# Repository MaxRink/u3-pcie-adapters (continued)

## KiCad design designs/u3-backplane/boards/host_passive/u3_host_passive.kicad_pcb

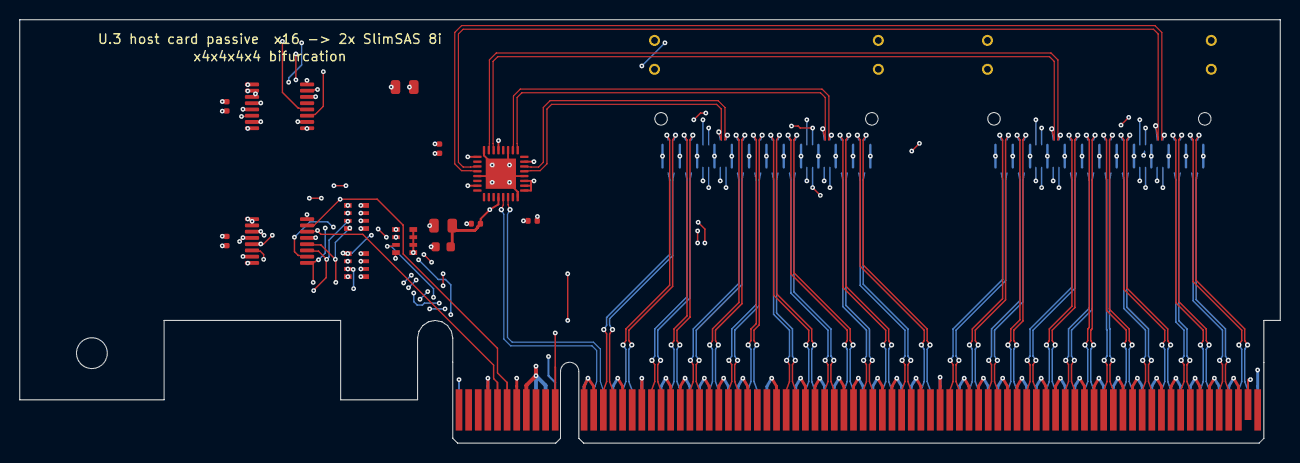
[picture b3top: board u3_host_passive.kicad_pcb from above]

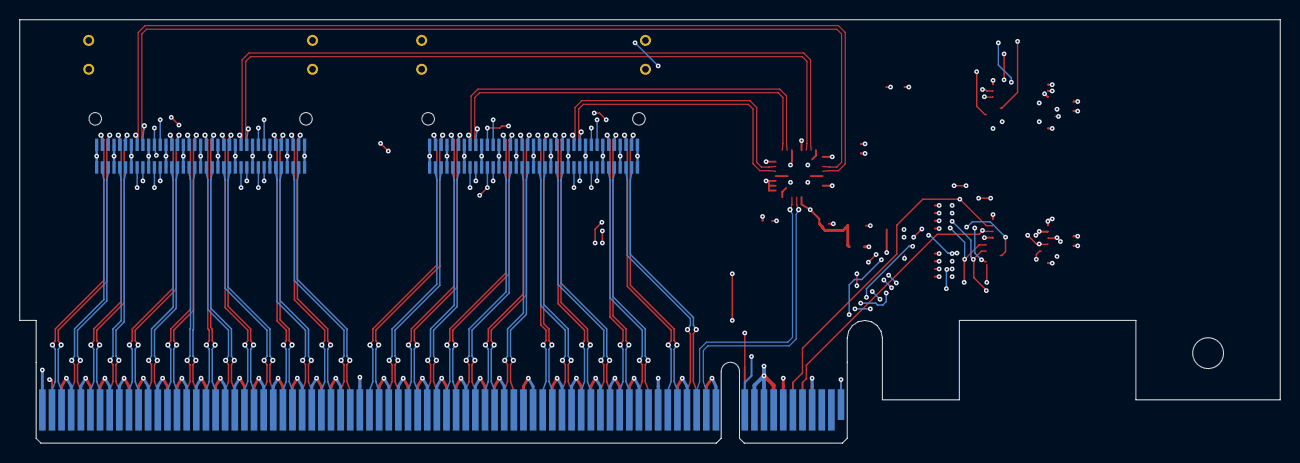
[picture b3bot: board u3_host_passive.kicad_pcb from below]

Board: 6 copper layers, 131.0 x 44.0 mm, 18 parts (2 on the bottom side), 102 nets.

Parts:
C1, C2, C4, C5, C6: 100nF; C_0402_1005Metric
C3, C7: 10uF 25V X5R; C_0805_2012Metric
FB1: ferrite 600R@100MHz; L_0603_1608Metric
H1: bracket; MountingHole_3.2mm_M3
J1: PCIe x16 edge; BUS_PCIexpress_x16
J2, J3: U10A474240T; Amphenol_U10A474_SlimSAS_8i_SFF-8654_RA_SMD
RN1, RN2: 4.7k x4; R_Array_Convex_4x0603
RN3: 33R x4; R_Array_Convex_4x0603
U1: 9DBL0442BKILF; VQFN-32-1EP_5x5mm_P0.5mm_EP3.15x3.15mm
U2: TCA9546APWR; TSSOP-16_4.4x5mm_P0.65mm
U3: TCA9554PWR; TSSOP-16_4.4x5mm_P0.65mm

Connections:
3V3: C1.2, C2.2, C3.1, C4.1, C5.1, FB1.1, J1.A9, J1.A10, J1.B8, RN1.5, RN1.6, RN1.7, RN1.8, RN2.5, RN2.6, RN2.7, RN2.8, U1.9, U1.10, U1.11, U1.15, U1.25, U1.31, U2.1, U2.2, U2.13, U2.16, U3.1, U3.2, U3.3, U3.16
3V3_A: C6.2, C7.2, FB1.2, U1.4, U1.21
GND: C1.1, C2.1, C3.2, C4.2, C5.2, C6.1, C7.1, J1.A4, J1.A12, J1.A15, J1.A18, J1.A20, J1.A23, J1.A24, J1.A27, J1.A28, J1.A31, J1.A34, J1.A37, J1.A38, J1.A41, J1.A42, J1.A45, J1.A46, J1.A49, J1.A51, J1.A54, J1.A55, J1.A58, J1.A59, J1.A62, J1.A63, J1.A66, J1.A67, J1.A70, J1.A71, J1.A74, J1.A75, J1.A78, J1.A79, J1.A82, J1.B4, J1.B7, J1.B12, J1.B13, J1.B16, J1.B18, J1.B21, J1.B22, J1.B25, J1.B26, J1.B29, J1.B32, J1.B35, J1.B36, J1.B39, J1.B40, J1.B43, J1.B44, J1.B47, J1.B49, J1.B52, J1.B53, J1.B56, J1.B57, J1.B60, J1.B61, J1.B64, J1.B65, J1.B68, J1.B69, J1.B72, J1.B73, J1.B76, J1.B77, J1.B80, J2.A1, J2.A4, J2.A7, J2.A10, J2.A13, J2.A16, J2.A19, J2.A22, J2.A25, J2.A28, J2.A31, J2.A34, J2.A37, J2.B1, J2.B4, J2.B7, J2.B10, J2.B13, J2.B16, J2.B19, J2.B22, J2.B25, J2.B28, J2.B31, J2.B34, J2.B37, J2.SH, J3.A1, J3.A4, J3.A7, J3.A10, J3.A13, J3.A16, J3.A19, J3.A22, J3.A25, J3.A28, J3.A31, J3.A34, J3.A37, J3.B1, J3.B4, J3.B7, J3.B10, J3.B13, J3.B16, J3.B19, J3.B22, J3.B25, J3.B28, J3.B31, J3.B34, J3.B37, J3.SH, U1.8, U1.12, U1.19, U1.24, U1.29, U1.33, U2.8, U3.8
P0_BPTYPE: J2.A8, U3.9
P0_CPRSNT_N: J2.B12, U3.4
P0_PERST_N: J2.B11, RN3.1
P0_SCL: J2.B8, RN1.2, U2.5
P0_SDA: J2.B9, RN1.1, U2.4
P1_BPTYPE: J2.A26, U3.10
P1_CPRSNT_N: J2.B30, U3.5
P1_PERST_N: J2.B29, RN3.2
P1_SCL: J2.B26, RN1.4, U2.7
P1_SDA: J2.B27, RN1.3, U2.6
P2_BPTYPE: J3.A8, U3.11
P2_CPRSNT_N: J3.B12, U3.6
P2_PERST_N: J3.B11, RN3.3
P2_SCL: J3.B8, RN2.2, U2.10
P2_SDA: J3.B9, RN2.1, U2.9
P3_BPTYPE: J3.A26, U3.12
P3_CPRSNT_N: J3.B30, U3.7
P3_PERST_N: J3.B29, RN3.4
P3_SCL: J3.B26, RN2.4, U2.12
P3_SDA: J3.B27, RN2.3, U2.11
PCIE_RST_N: J1.A11, RN3.5, RN3.6, RN3.7, RN3.8, U2.3
PCIE_WAKE_N: J1.B11, J2.A9, J2.A27, J3.A9, J3.A27
PER0_N: J1.A17, J2.A3
PER0_P: J1.A16, J2.A2
PER1_N: J1.A22, J2.A6
PER1_P: J1.A21, J2.A5
PER2_N: J1.A26, J2.A15
PER2_P: J1.A25, J2.A14
PER3_N: J1.A30, J2.A18
PER3_P: J1.A29, J2.A17
PER4_N: J1.A36, J2.A21
PER4_P: J1.A35, J2.A20
PER5_N: J1.A40, J2.A24
PER5_P: J1.A39, J2.A23
PER6_N: J1.A44, J2.A33
PER6_P: J1.A43, J2.A32
PER7_N: J1.A48, J2.A36
PER7_P: J1.A47, J2.A35
PER8_N: J1.A53, J3.A3
PER8_P: J1.A52, J3.A2
PER9_N: J1.A57, J3.A6
PER9_P: J1.A56, J3.A5
PER10_N: J1.A61, J3.A15
PER10_P: J1.A60, J3.A14
PER11_N: J1.A65, J3.A18
PER11_P: J1.A64, J3.A17
PER12_N: J1.A69, J3.A21
PER12_P: J1.A68, J3.A20
PER13_N: J1.A73, J3.A24
PER13_P: J1.A72, J3.A23
PER14_N: J1.A77, J3.A33
PER14_P: J1.A76, J3.A32
PER15_N: J1.A81, J3.A36
PER15_P: J1.A80, J3.A35
PET0_N: J1.B15, J2.B3
PET0_P: J1.B14, J2.B2
PET1_N: J1.B20, J2.B6
PET1_P: J1.B19, J2.B5
PET2_N: J1.B24, J2.B15
PET2_P: J1.B23, J2.B14
PET3_N: J1.B28, J2.B18
PET3_P: J1.B27, J2.B17
PET4_N: J1.B34, J2.B21
PET4_P: J1.B33, J2.B20
PET5_N: J1.B38, J2.B24
PET5_P: J1.B37, J2.B23
PET6_N: J1.B42, J2.B33
PET6_P: J1.B41, J2.B32
PET7_N: J1.B46, J2.B36
PET7_P: J1.B45, J2.B35
PET8_N: J1.B51, J3.B3
PET8_P: J1.B50, J3.B2
PET9_N: J1.B55, J3.B6
PET9_P: J1.B54, J3.B5
PET10_N: J1.B59, J3.B15
PET10_P: J1.B58, J3.B14
PET11_N: J1.B63, J3.B18
PET11_P: J1.B62, J3.B17
PET12_N: J1.B67, J3.B21
PET12_P: J1.B66, J3.B20
PET13_N: J1.B71, J3.B24
PET13_P: J1.B70, J3.B23
PET14_N: J1.B75, J3.B33
PET14_P: J1.B74, J3.B32
PET15_N: J1.B79, J3.B36
PET15_P: J1.B78, J3.B35
PRSNT_N: J1.A1, J1.B81
REFCLK0_N: J2.A12, U1.14
REFCLK0_P: J2.A11, U1.13
REFCLK1_N: J2.A30, U1.18
REFCLK1_P: J2.A29, U1.17
REFCLK2_N: J3.A12, U1.23
REFCLK2_P: J3.A11, U1.22
REFCLK3_N: J3.A30, U1.28
REFCLK3_P: J3.A29, U1.27
REFCLK_IN_N: J1.A14, U1.6
REFCLK_IN_P: J1.A13, U1.5
SMCLK: J1.B5, U2.14, U3.14
SMDAT: J1.B6, U2.15, U3.15

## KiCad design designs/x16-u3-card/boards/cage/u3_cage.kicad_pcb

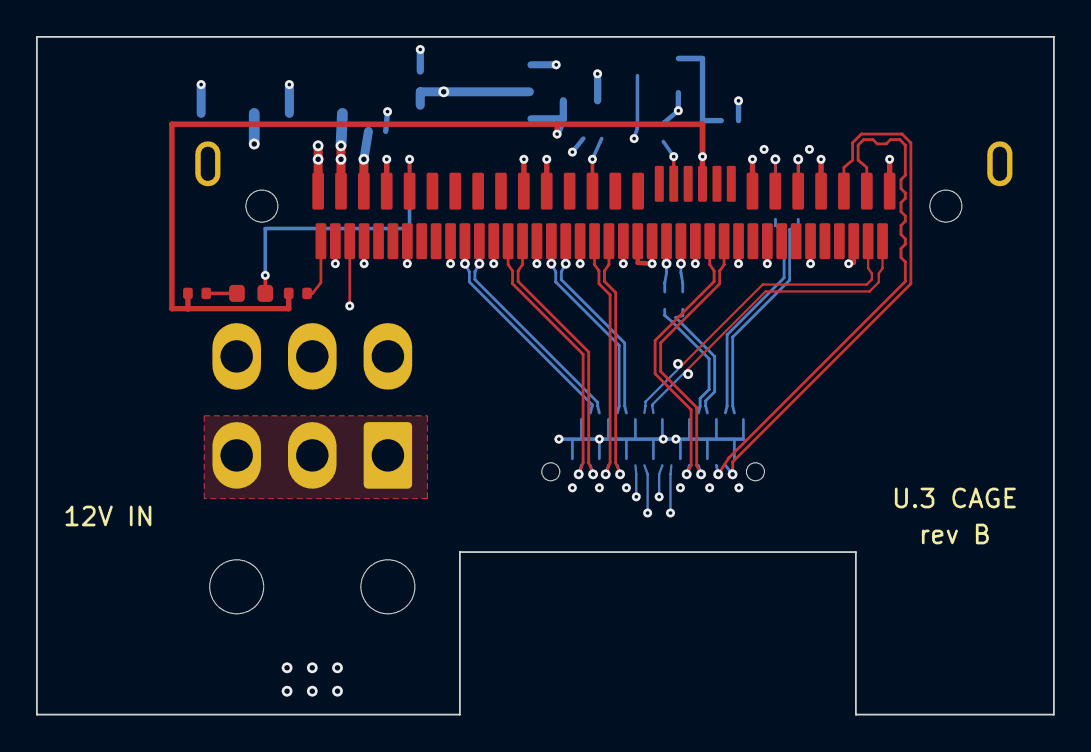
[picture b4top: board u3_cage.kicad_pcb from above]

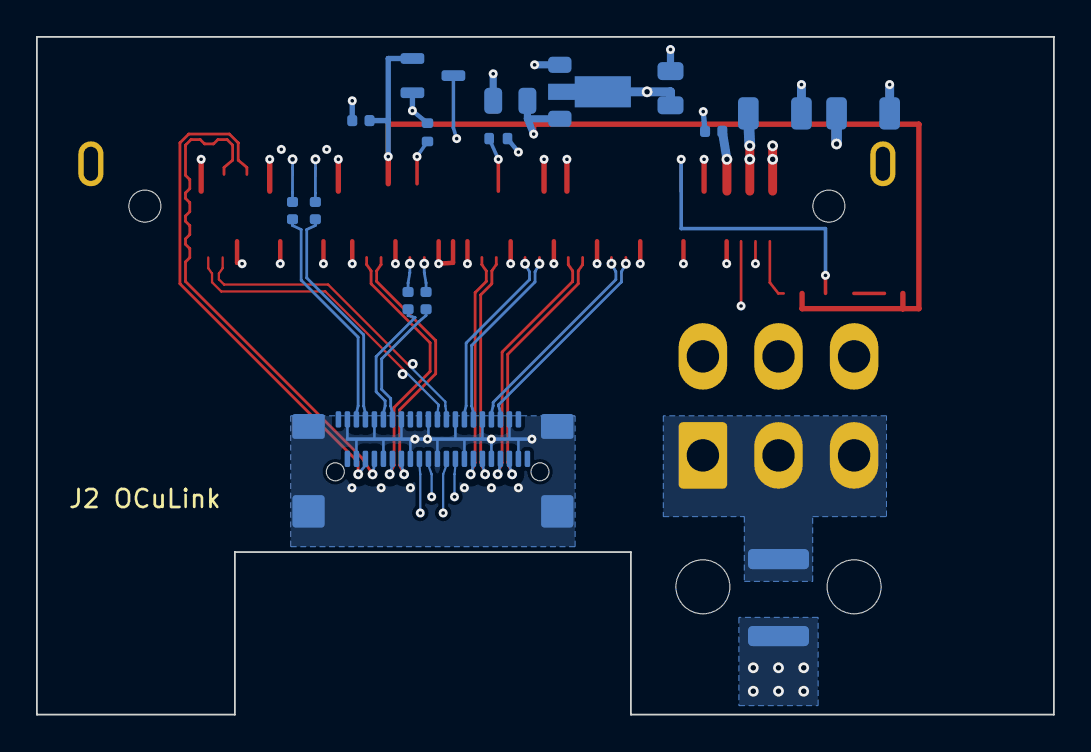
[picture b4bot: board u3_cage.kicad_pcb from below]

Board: 6 copper layers, 56.5 x 37.7 mm, 25 parts (16 on the bottom side), 34 nets.

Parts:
C1, C2: 22uF 25V X5R; C_1206_3216Metric
C3: 100nF 50V X7R; C_0402_1005Metric
C4, C5: 10uF 25V X5R; C_0805_2012Metric
C6: 100nF; C_0402_1005Metric
C11, C12, C13, C14: 220nF 16V X7R; C_0402_1005Metric
D2: KT-0603YG; LED_0603_1608Metric
F1: mSMD300-16V (3 A hold); Fuse_1812_4532Metric
H1, H2, H3, H4: M3 slot; MountingSlot_M3_3.2x6.2
J1: PSAS4F2130021TR; Amphenol_PSAS4F213002_SFF-8639_U3_RA_SMD
J2: G14A421211112HR; Amphenol_G14A421211112HR_OCuLink_4i_RA_SMD
J3: PCIe 6-pin 45558-0003; Molex_Mini-Fit_Jr_5569-06A2_2x03_P4.20mm_Horizontal
Q1: 2N7002; SOT-23-3
R3, R4: 10k; R_0402_1005Metric
R5: 1k; R_0402_1005Metric
R6: 100k; R_0402_1005Metric
U1: MCP1703AT-3302E/MB; SOT-89-3

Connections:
3V3_AUX: C5.2, C6.2, J1.E3, Q1.1, R4.1, R5.1, U1.3
12V: C1.1, C2.1, C3.2, C4.1, F1.1, J1.P13, J1.P14, J1.P15, U1.2
12V_IN: F1.2, J3.1, J3.2, J3.3
ACT_N: D2.1, J1.P11
CPRSNT_N: J2.A13, Q1.3
C_PER0_N: C12.1, J2.B3
C_PER0_P: C11.1, J2.B4
C_PER1_N: C14.1, J2.B6
C_PER1_P: C13.1, J2.B7
DUALPORTEN_N: J1.E25, R4.2
GND: C1.2, C2.2, C3.1, C4.2, C5.1, C6.1, J1.E9, J1.E12, J1.E15, J1.E19, J1.E22, J1.MP, J1.P5, J1.P6, J1.P12, J1.S1, J1.S4, J1.S7, J1.S8, J1.S11, J1.S14, J1.S15, J1.S16, J1.S19, J1.S22, J1.S25, J1.S28, J2.A2, J2.A5, J2.A8, J2.A11, J2.A14, J2.A17, J2.A20, J2.B2, J2.B5, J2.B8, J2.B11, J2.B14, J2.B17, J2.B20, J2.SH, J3.4, J3.5, J3.6, Q1.2, R3.2, R6.2, U1.1
LED_A: D2.2, R5.2
PCIE_RST_N: J1.E5, J2.A12, R6.1
PER0_N: C12.2, J1.S5
PER0_P: C11.2, J1.S6
PER1_N: C14.2, J1.S12
PER1_P: C13.2, J1.S13
PER2_N: J1.S20, J2.B15
PER2_P: J1.S21, J2.B16
PER3_N: J1.S26, J2.B18
PER3_P: J1.S27, J2.B19
PET0_N: J1.S3, J2.A3
PET0_P: J1.S2, J2.A4
PET1_N: J1.S10, J2.A7
PET1_P: J1.S9, J2.A6
PET2_N: J1.S18, J2.A16
PET2_P: J1.S17, J2.A15
PET3_N: J1.S24, J2.A19
PET3_P: J1.S23, J2.A18
PWRDIS: J1.P3, R3.1
REFCLK0_N: J1.E8, J2.B13
REFCLK0_P: J1.E7, J2.B12
SMBCLK: J1.E23, J2.A9
SMBDAT: J1.E24, J2.A10

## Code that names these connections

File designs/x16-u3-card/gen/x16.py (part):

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# so no stub crosses a row.
YCV = -12.55               # slot clock via row
SLOT = [  # net, pin layer, pin, via xy, band row, column x, channel row, width
    ("PCIE_WAKE_N", "L6", 11, (xpin(11) - 0.55, -13.0), -11.55, 252.3 - 312.0 + XM, -16.7, 0.15),
    ("PCIE_RST_N", "L1", 11, (xpin(11), -12.3), -11.25, 251.9 - 312.0 + XM, -16.3, 0.15),
    ("3V3_AUX_SLOT", "L6", 10, (xpin(10), -12.3), -10.9, 251.4 - 312.0 + XM, -15.8, 0.25),
    ("3V3", "L1", 9, (xpin(9), -12.3), -10.35, 250.8 - 312.0 + XM, -15.25, 0.4),
    ("SMDAT_SLOT", "L6", 6, (xpin(6), -12.3), -9.8, 250.25 - 312.0 + XM, -14.7, 0.15),
    ("SMCLK_SLOT", "L6", 5, (xpin(5), -12.3), -9.4, 249.85 - 312.0 + XM, -14.3, 0.15)]
SLOTV = {}
ROWS = {}
for net, L, pin, (vx, vy), yb, xcol, yrow, w_ in SLOT:
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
